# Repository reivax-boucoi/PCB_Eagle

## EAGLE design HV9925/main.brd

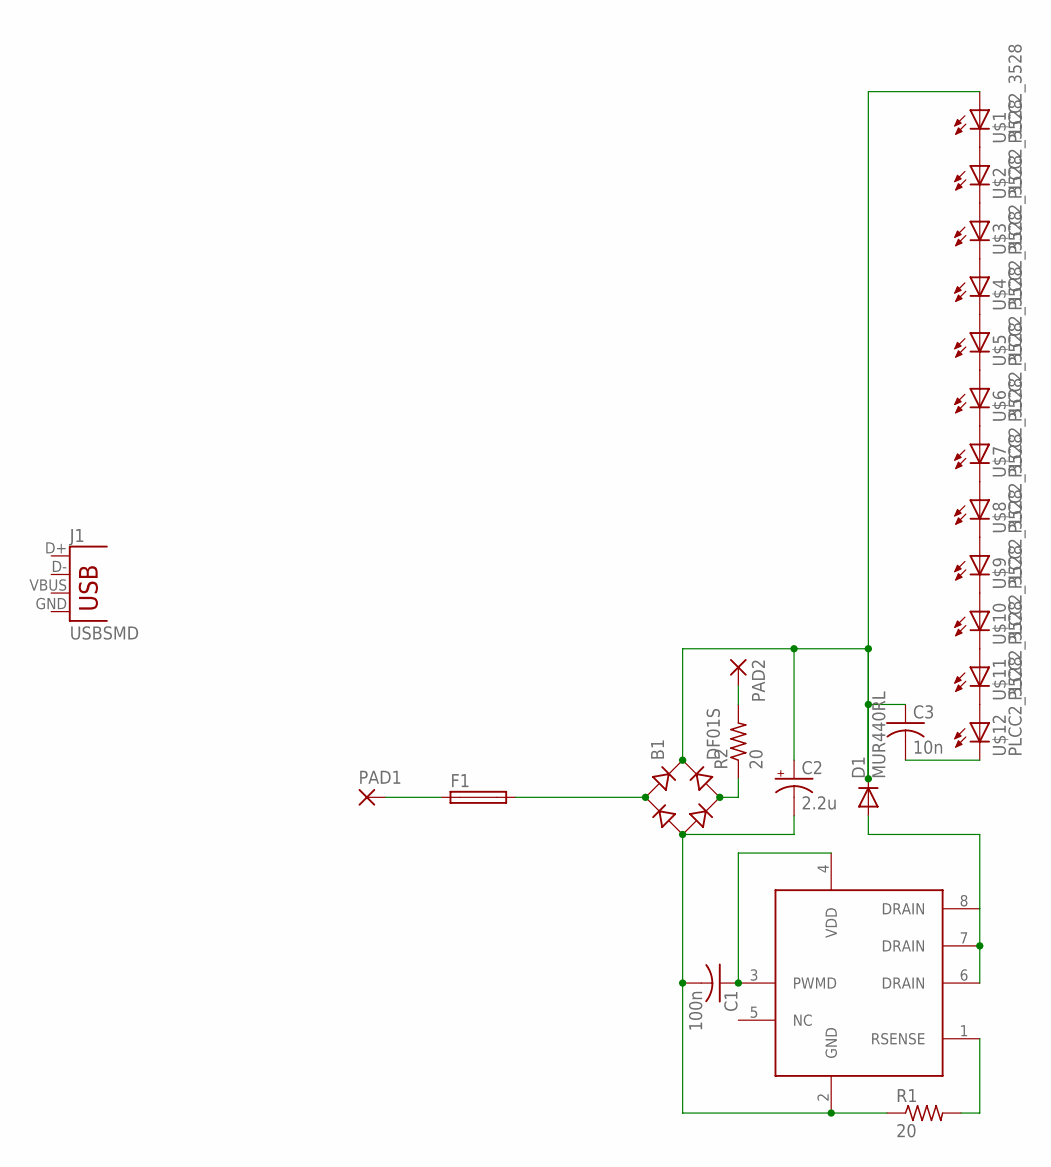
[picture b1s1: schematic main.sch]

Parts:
B1: DF01S; DFS
C1: 100n; C0603
C2: 2.2u; E3,5-8
C3: 10n; C025-025X050
D1: MUR440RL; C2673
F1: TE5
J1: USBSMD; USB-MINIB
PAD1, PAD2: 2,54/1,0
R1, R2: 20; R0805
U$1, U$2, U$3, U$4, U$5, U$6, U$7, U$8, U$9, U$10, U$11, U$12: PLCC2_3528
U$13: HV9925; SOIC-8

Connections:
unnamed: U$1.P$2 (C), U$2.P$1 (A)
unnamed: U$2.P$2 (C), U$3.P$1 (A)
unnamed: U$3.P$2 (C), U$4.P$1 (A)
unnamed: U$4.P$2 (C), U$5.P$1 (A)
unnamed: U$5.P$2 (C), U$6.P$1 (A)
unnamed: U$6.P$2 (C), U$7.P$1 (A)
unnamed: U$7.P$2 (C), U$8.P$1 (A)
unnamed: U$8.P$2 (C), U$9.P$1 (A)
unnamed: U$9.P$2 (C), U$10.P$1 (A)
unnamed: U$10.P$2 (C), U$11.P$1 (A)
unnamed: U$11.P$2 (C), U$12.P$1 (A)
unnamed: B1.AC1, F1.2
unnamed: PAD2.1, R2.2
unnamed: B1.+, C2.+, C3.1, D1.C, U$1.P$1 (A)
unnamed: B1.-, C1.2, C2.-, R1.1, U$13.2 (GND)
unnamed: F1.1, PAD1.1
unnamed: D1.A, U$13.6 (DRAIN), U$13.7 (DRAIN), U$13.8 (DRAIN)
unnamed: B1.AC2, R2.1
unnamed: C1.1, U$13.3 (PWMD), U$13.4 (VDD)
unnamed: R1.2, U$13.1 (RSENSE)
unnamed: C3.2, U$12.P$2 (C)

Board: 2 copper layers, 24 parts (0 on the bottom side), 21 nets, no tracks yet.

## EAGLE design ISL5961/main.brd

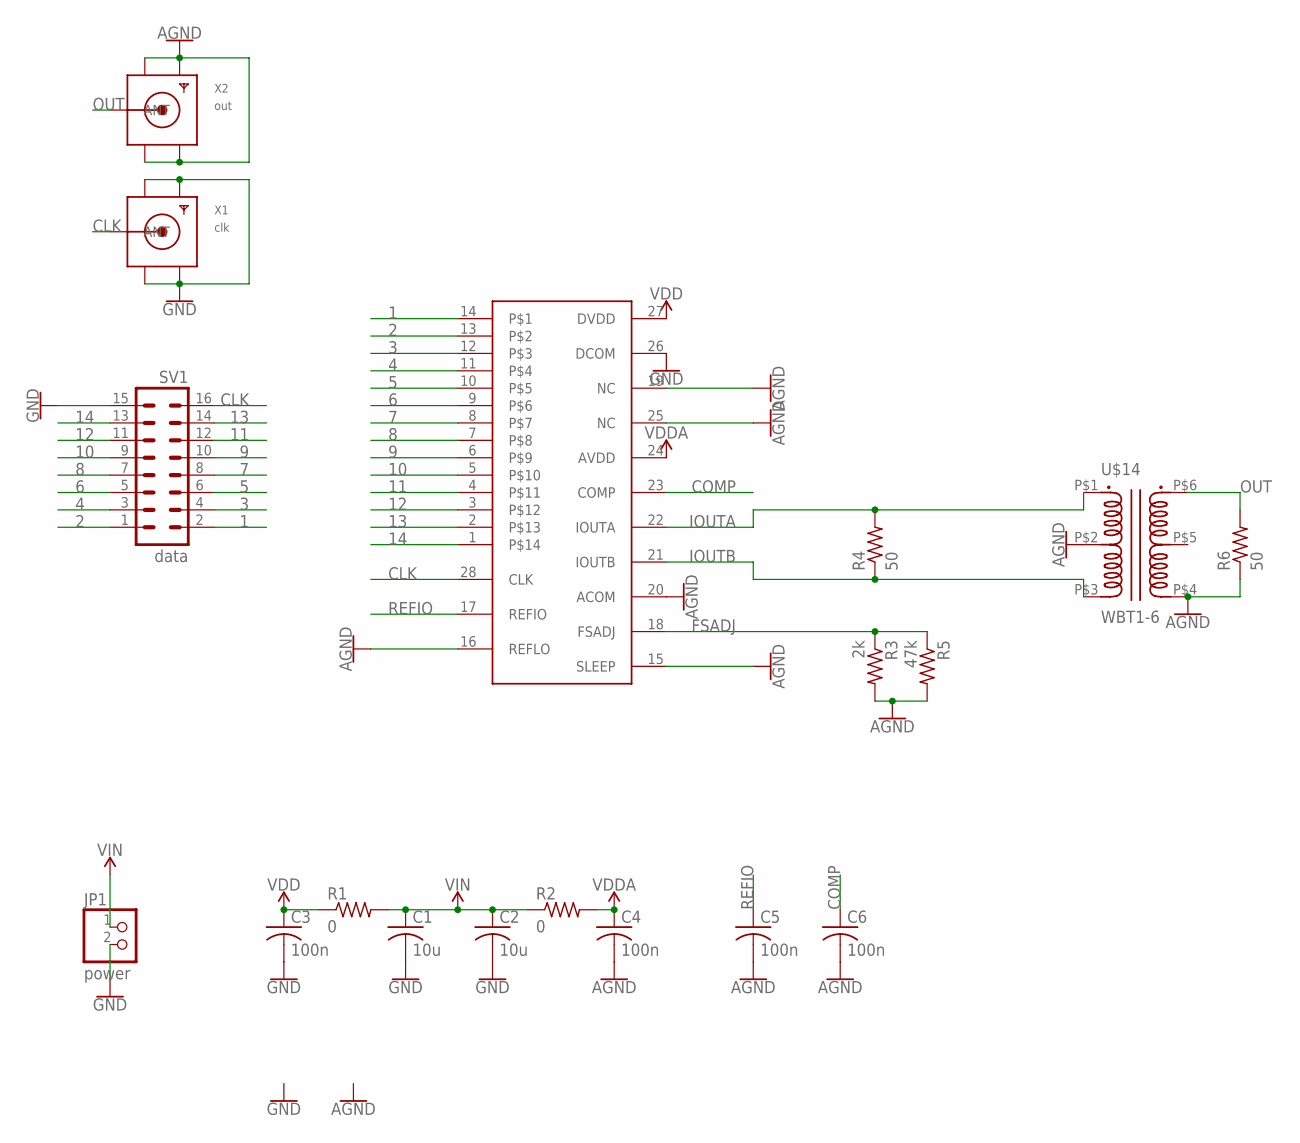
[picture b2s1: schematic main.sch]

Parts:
C1, C2: 10u; C0805K
C3, C4, C5, C6: 100n; C0603K
JP1: power; 1X02
R1, R2: 0; 0309/10
R3: 2k; R0603
R4, R6: 50; R0603
R5: 47k; R0603
SV1: data; MA08-2
U$1: ISL5961; TSSOP28
U$14: WBT1-6
X1: clk; SMA_EDGELAUNCH
X2: out; SMA_EDGELAUNCH

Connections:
1: SV1.2, U$1.14
2: SV1.1, U$1.13
3: SV1.4, U$1.12
4: SV1.3, U$1.11
5: SV1.6, U$1.10
6: SV1.5, U$1.9
7: SV1.8, U$1.8
8: SV1.7, U$1.7
9: SV1.10, U$1.6
10: SV1.9, U$1.5
11: SV1.12, U$1.4
12: SV1.11, U$1.3
13: SV1.14, U$1.2
14: SV1.13, U$1.1
AGND: C4.2, C5.2, C6.2, R3.2, R5.2, R6.1, U$1.15 (SLEEP), U$1.16 (REFLO), U$1.19 (NC), U$1.20 (ACOM), U$1.25 (NC), U$14.P$2 (1M), U$14.P$4 (2B), X2.GND@1 (GND4), X2.GND@2 (GND3), X2.GND@3 (GND2), X2.GND@4 (GND1)
CLK: SV1.16, U$1.28 (CLK), X1.P (ANT)
COMP: C6.1, U$1.23 (COMP)
FSADJ: R3.1, R5.1, U$1.18 (FSADJ)
GND: C1.2, C2.2, C3.2, JP1.2, SV1.15, U$1.26 (DCOM), X1.GND@1 (GND4), X1.GND@2 (GND3), X1.GND@3 (GND2), X1.GND@4 (GND1)
IOUTA: R4.2, U$1.22 (IOUTA), U$14.P$1 (1A)
IOUTB: R4.1, U$1.21 (IOUTB), U$14.P$3 (1B)
OUT: R6.2, U$14.P$6 (2A), X2.P (ANT)
REFIO: C5.1, U$1.17 (REFIO)
VDD: C3.1, R1.1, U$1.27 (DVDD)
VDDA: C4.1, R2.2, U$1.24 (AVDD)
VIN: C1.1, C2.1, JP1.1, R1.2, R2.1

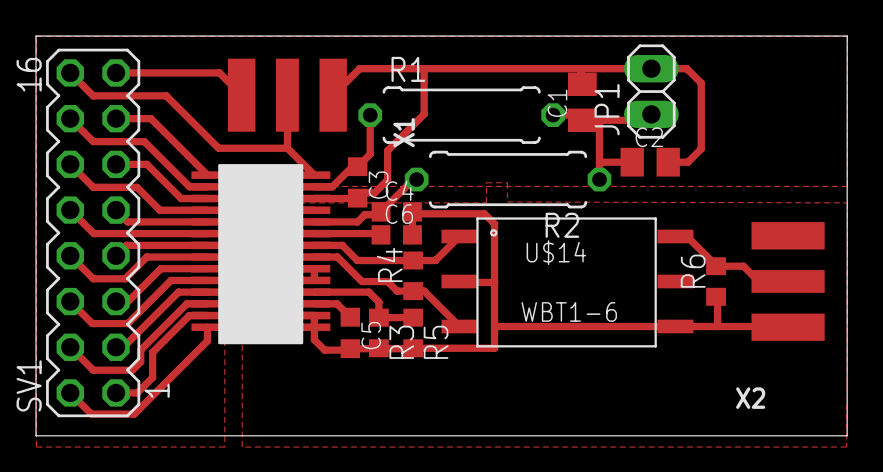
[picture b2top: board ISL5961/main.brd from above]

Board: 2 copper layers, 45.1 x 22.2 mm, 18 parts (0 on the bottom side), 26 nets.

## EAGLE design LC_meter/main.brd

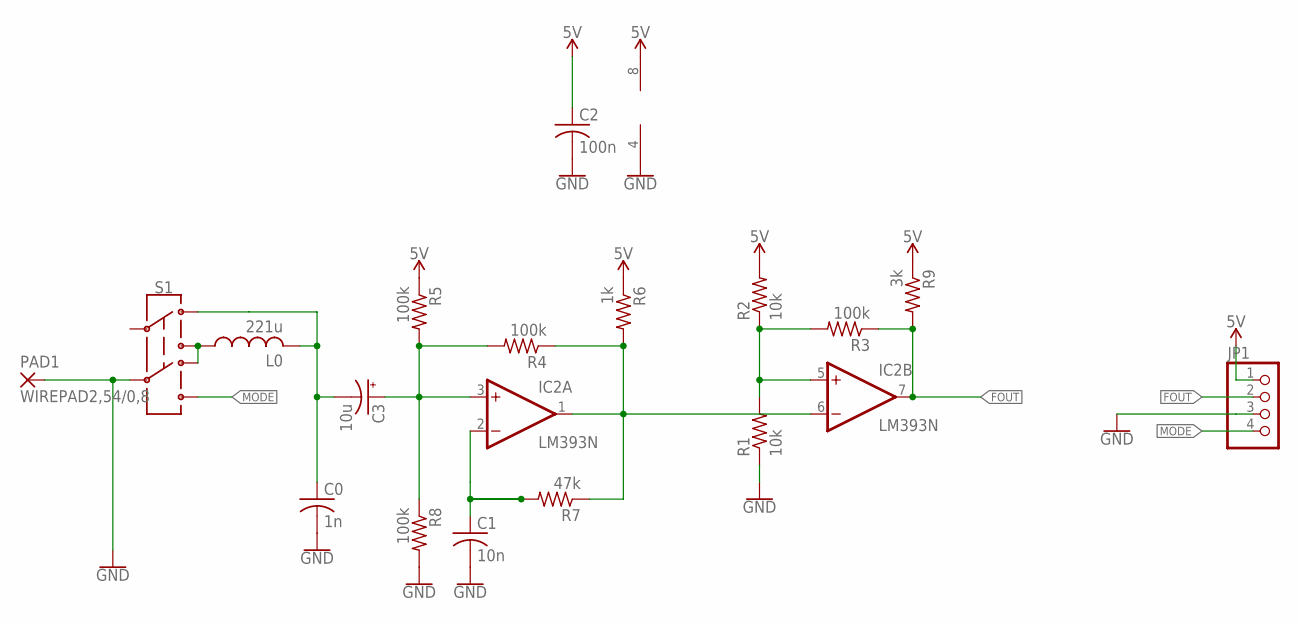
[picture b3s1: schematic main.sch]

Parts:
C0: 1n; C025-025X050
C1: 10n; C025-025X050
C2: 100n; C025-025X050
C3: 10u; E2,5-6
IC2: LM393N; DIL08
JP1: PINHD-1X4; 1X04
L0: 221u; 0204/5
PAD1: WIREPAD2,54/0,8; 2,54/0,8
R1: 10k; 0204/7
R2: 10k; 0207/10
R3, R4, R5, R8: 100k; 0207/10
R6: 1k; 0207/10
R7: 47k; 0207/10
R9: 3k; 0207/10
S1: SWITCH-DPDT-PTH-GPI-152-3013; SWITCH_DPDT_PTH_GPI-152-3013

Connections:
5V: C2.1, IC2.8 (V+), JP1.1, R2.2, R5.1, R6.1, R9.1
FOUT: IC2.7 (OUT), JP1.2, R3.1, R9.2
GND: C0.2, C1.2, C2.2, IC2.4 (V-), JP1.3, PAD1.1, R1.1, R8.2, S1.C@2 (5)
MODE: JP1.4, S1.21 (6)
unnamed: C1.1, IC2.2 (-IN), R7.2
unnamed: C3.+, IC2.3 (+IN), R4.2, R5.2, R8.1
unnamed: IC2.1 (OUT), IC2.6 (-IN), R4.1, R6.2, R7.1
unnamed: IC2.5 (+IN), R1.2, R2.1, R3.2
unnamed: C0.1, C3.-, L0.2, S1.10 (1)
unnamed: L0.1, S1.11 (4), S1.20 (3)

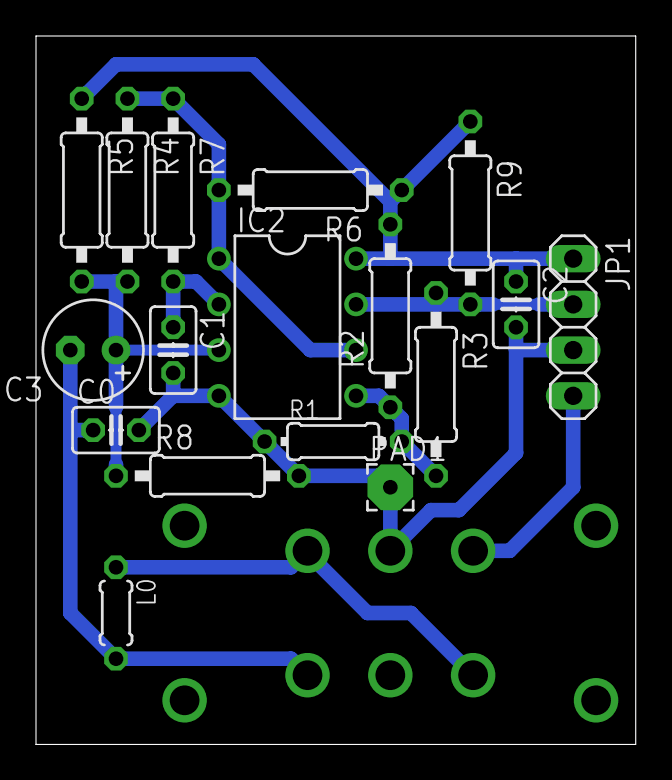
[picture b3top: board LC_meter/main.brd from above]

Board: 2 copper layers, 33.3 x 39.4 mm, 18 parts (1 on the bottom side), 10 nets.

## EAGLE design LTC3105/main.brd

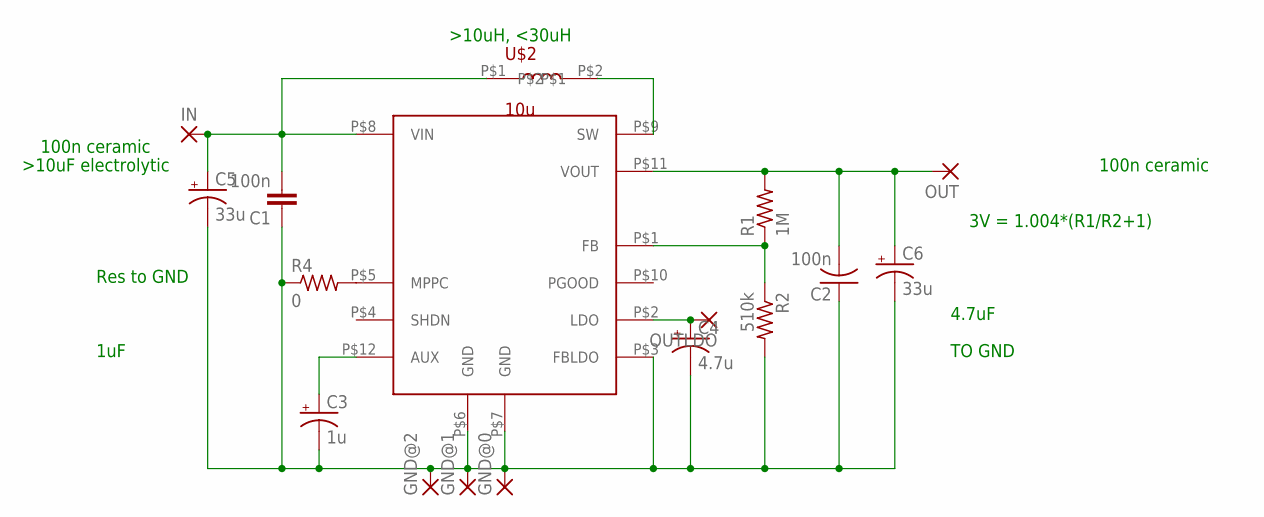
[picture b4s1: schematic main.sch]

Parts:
C1: 100n; C0603
C2: 100n; C025-025X050
C3: 1u; E1,8-4
C4: 4.7u; E1,8-4
C5, C6: 33u; E2-5
GND@0, GND@1, GND@2: 2,54/1,0
IN: 2,54/1,0
OUT: 2,54/1,0
OUTLDO: 2,54/1,0
R1: 1M; 0204V
R2: 510k; R0603
R4: 0; R0603
U$1: LTC3105; MSOP_12
U$2: 10u; DR0810

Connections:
GND: C1.1, C2.1, C3.-, C4.-, C5.-, C6.-, GND@0.1, GND@1.1, GND@2.1, R2.2, R4.1, U$1.P$3 (FBLDO), U$1.P$6 (GND), U$1.P$7 (GND)
unnamed: C4.+, OUTLDO.1, U$1.P$2 (LDO)
unnamed: R1.1, R2.1, U$1.P$1 (FB)
unnamed: C3.+, U$1.P$12 (AUX)
unnamed: C1.2, C5.+, IN.1, U$1.P$8 (VIN), U$2.P$1
unnamed: U$1.P$9 (SW), U$2.P$2
unnamed: C2.2, C6.+, OUT.1, R1.2, U$1.P$11 (VOUT)
unnamed: R4.2, U$1.P$5 (MPPC)

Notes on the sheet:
100n ceramic
1uF
3V = 1.004*(R1/R2+1)
Res to GND
TO GND
4.7uF

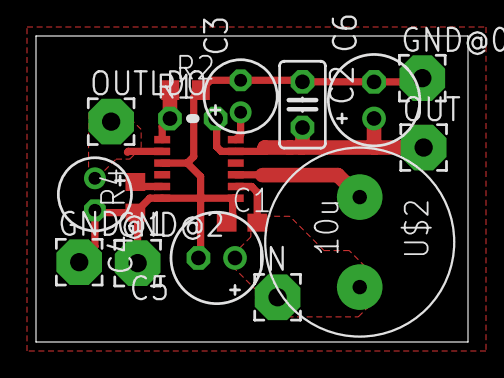
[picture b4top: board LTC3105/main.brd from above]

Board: 2 copper layers, 24.0 x 17.0 mm, 17 parts (0 on the bottom side), 8 nets.

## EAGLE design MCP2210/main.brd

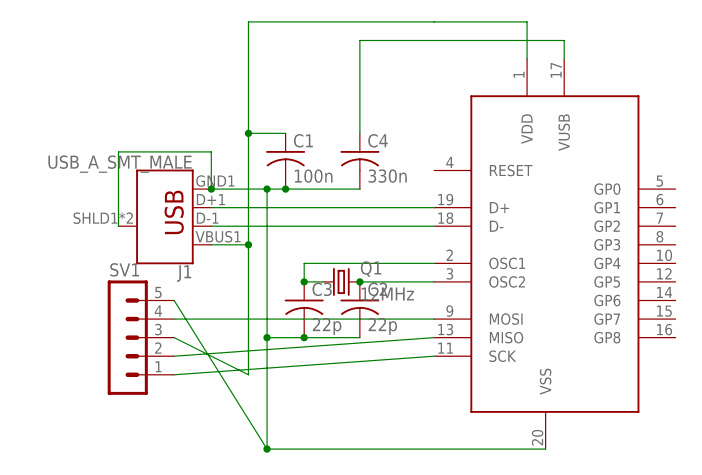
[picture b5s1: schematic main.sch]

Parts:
C1: 100n; C0805
C2, C3: 22p; C0603
C4: 330n; C0603
J1: USB_A_SMT_MALE; USB-A-SMT-MALE
Q1: 12MHz; HC49U-V
SV1: MA05-1
U$1: MCP2210; SOIC20_GENERIC

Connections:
GND: C1.2, C2.2, C3.2, C4.2, J1.GND1 (GND), J1.SHLD1 (SHIELD), J1.SHLD2 (SHIELD), SV1.5, U$1.20 (VSS)
unnamed: J1.D+1 (D+), U$1.19 (D+)
unnamed: J1.D-1 (D-), U$1.18 (D-)
unnamed: C1.1, J1.VBUS1 (VBUS), SV1.3, U$1.1 (VDD)
unnamed: C3.1, Q1.1, U$1.2 (OSC1)
unnamed: C2.1, Q1.2, U$1.3 (OSC2)
unnamed: C4.1, U$1.17 (VUSB)
unnamed: SV1.1, U$1.11 (SCK)
unnamed: SV1.2, U$1.13 (MISO)
unnamed: SV1.4, U$1.9 (MOSI)

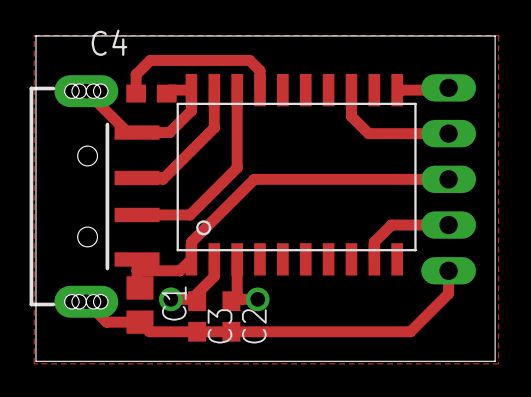
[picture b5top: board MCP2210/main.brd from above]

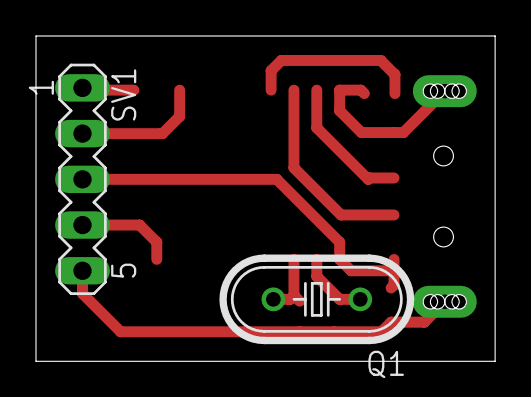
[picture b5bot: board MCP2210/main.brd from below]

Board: 2 copper layers, 25.5 x 18.1 mm, 8 parts (2 on the bottom side), 10 nets.

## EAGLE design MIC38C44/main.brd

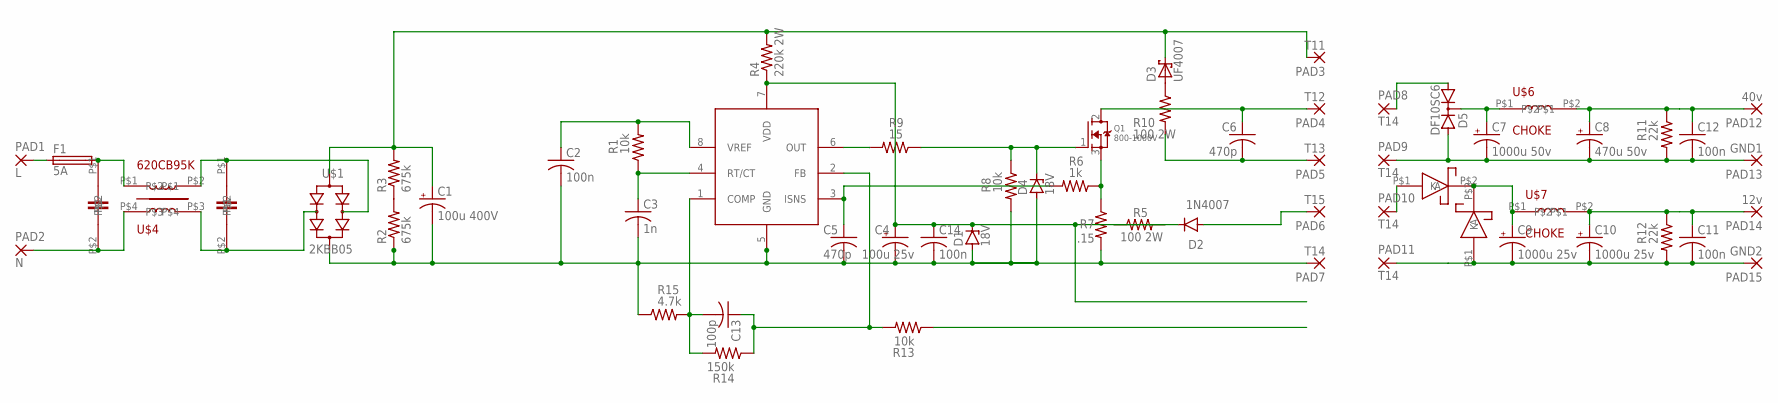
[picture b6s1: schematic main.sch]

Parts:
C1: 100u 400V; EB25D
C2, C11, C12, C14: 100n; C050-035X075
C3: 1n; C050-035X075
C4: 100u 25v; E2,5-6
C5, C6: 470p; C050-035X075
C7: 1000u 50v; E5-13
C8: 470u 50v; E5-10,5
C9, C10: 1000u 25v; E5-10,5
C13: 100p; C050-035X075
D1, D4: 18V; ZDIO-7.5
D2: 1N4007; DO41-10
D3: UF4007; DO35-7
D5: DF10SC6; TO220ABS
D7, D8: SS34; DO-214AB
F1: 5A; SH22,5
PAD1: L; 2,54/1,0
PAD2: N; 2,54/1,0
PAD3: T11; 2,54/1,0
PAD4: T12; 2,54/1,0
PAD5: T13; 2,54/1,0
PAD6: T15; 2,54/1,0
PAD7, PAD8, PAD9, PAD10, PAD11: T14; 2,54/1,0
PAD12: 40v; 2,54/1,0
PAD13: GND1; 2,54/1,0
PAD14: 12v; 2,54/1,0
PAD15: GND2; 2,54/1,0
Q1: 800-1000V; TO220V
R1, R8, R13: 10k; 0207/7
R2, R3: 675k; 0207/7
R4: 220k 2W; P0613/15
R5, R10: 100 2W; 0617V
R6: 1k; 0207/10
R7: .15; 0207/7
R9: 15; 0207/7
R11, R12: 22k; 0207/7
R14: 150k; 0207/7
R15: 4.7k; 0207/2V
U$1: 2KBB05
U$2, U$3: 100n; C_X2
U$4: 620CB95K; 602CB95K
U$5: MIC3844; DIL08
U$6, U$7: CHOKE

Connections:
12V: C10.+, C11.1, PAD14.1, R12.1, U$7.P$2
12VRECT: C9.+, D7.P$2 (K), D8.P$2 (K), U$7.P$1
40V: C8.+, C12.1, PAD12.1, R11.1, U$6.P$2
40VRECT: C7.+, D5.C, U$6.P$1
COMP: C13.2, R14.2, R15.2, U$5.1 (COMP)
DRAIN: Q1.3 (S), R6.1, R7.1
DRV: R9.2, U$5.6 (OUT)
FB: C13.1, R13.2, R14.1, U$5.2 (FB)
GATE: D4.C, Q1.1 (G), R8.1, R9.1
GND: C1.-, C2.2, C3.2, C4.-, C5.2, C14.2, D1.A, D4.A, PAD7.1, R2.1, R7.2, R8.2, R15.1, U$1.+, U$5.5 (GND)
GND1: C7.-, C8.-, C12.2, D5.A2, PAD9.1, PAD13.1, R11.2
GND2: C9.-, C10.-, C11.2, D7.P$1 (A), PAD11.1, PAD15.1, R12.2
unnamed: PAD2.1, U$3.P$2, U$4.P$4
unnamed: U$1.AC@1 (AC), U$2.P$2, U$4.P$3
unnamed: U$1.AC@2 (AC), U$2.P$1, U$4.P$2
unnamed: F1.2, U$3.P$1, U$4.P$1
unnamed: F1.1, PAD1.1
unnamed: R2.2, R3.1
unnamed: D2.C, R5.1
unnamed: C5.1, R6.2, U$5.3 (ISNS)
unnamed: D2.A, PAD6.1
unnamed: D3.A, R10.1
unnamed: C6.2, PAD5.1, R10.2
unnamed: D5.A1, PAD8.1
unnamed: D8.P$1 (A), PAD10.1
RTCT: C3.1, R1.1, U$5.4 (RT/CT)
SOURCE: C6.1, PAD4.1, Q1.2 (D)
V+: C1.+, D3.C, PAD3.1, R3.2, R4.2, U$1.-
VDD: C4.+, C14.1, D1.C, R4.1, R5.2, U$5.7 (VDD)
VREF: C2.1, R1.2, U$5.8 (VREF)

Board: 2 copper layers, 60 parts (0 on the bottom side), 30 nets, no tracks yet.

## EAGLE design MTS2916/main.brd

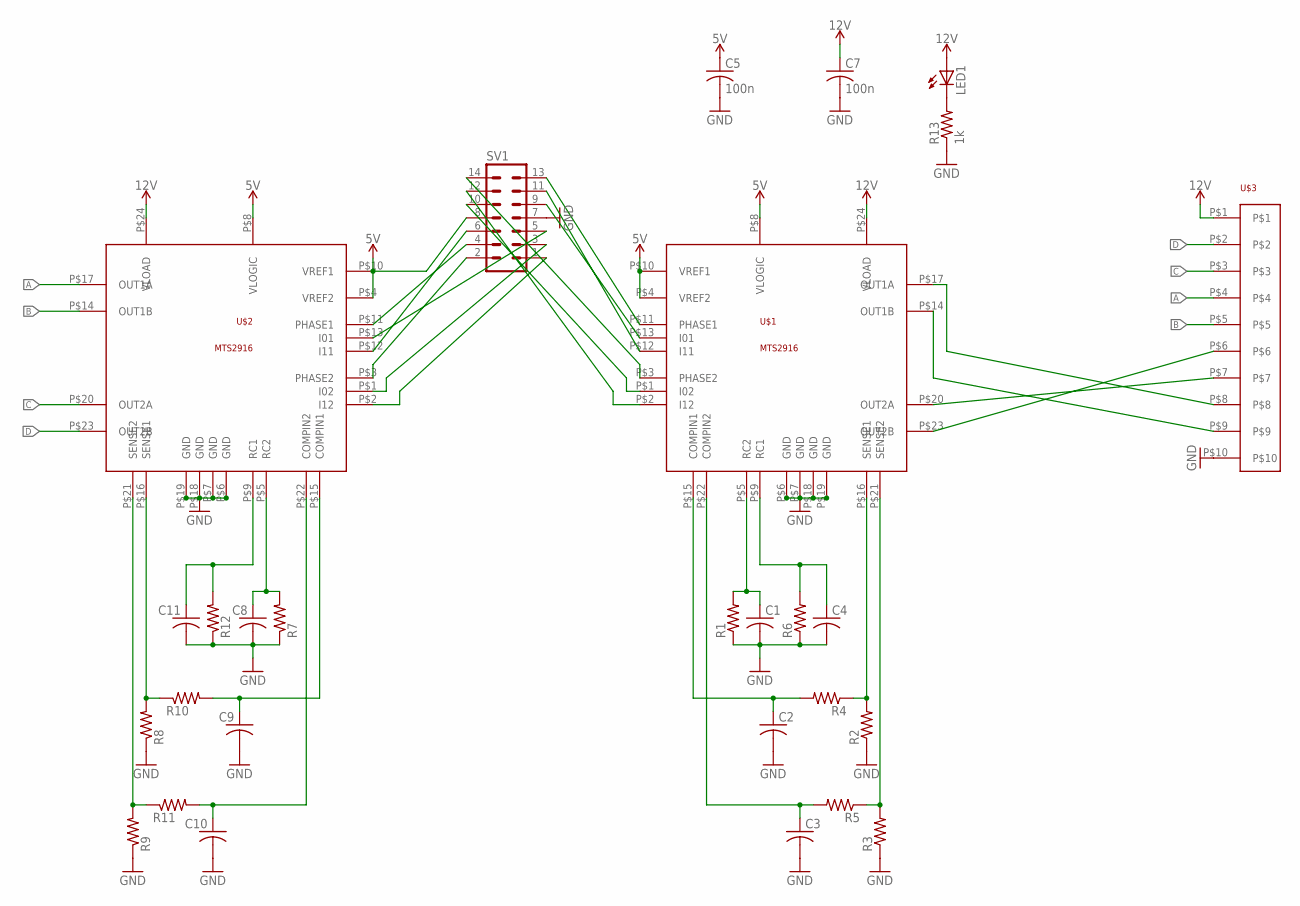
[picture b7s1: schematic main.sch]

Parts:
C1, C2, C3, C4, C8, C9, C10, C11: C-US025-024X044; C025-024X044
C5, C7: 100n; C0603
LED1: LED_ESML0603; LED_SML0603
R1, R2, R3, R4, R5, R6, R7, R8, R9, R10, R11, R12: R-US_M0805; M0805
R13: 1k; R0603
SV1: MA07-2
U$1, U$2: MTS2916; SOP24
U$3: SCREWTERM_5MM_10WAY

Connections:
5V: C5.1, SV1.8, U$1.P$4 (VREF2), U$1.P$8 (VLOGIC), U$1.P$10 (VREF1), U$2.P$4 (VREF2), U$2.P$8 (VLOGIC), U$2.P$10 (VREF1)
12V: C7.1, LED1.A, U$1.P$24 (VLOAD), U$2.P$24 (VLOAD), U$3.P$1
A: U$2.P$17 (OUT1A), U$3.P$4
B: U$2.P$14 (OUT1B), U$3.P$5
C: U$2.P$20 (OUT2A), U$3.P$3
D: U$2.P$23 (OUT2B), U$3.P$2
GND: C1.2, C2.2, C3.2, C4.2, C5.2, C7.2, C8.2, C9.2, C10.2, C11.2, R1.1, R2.1, R3.1, R6.1, R7.1, R8.1, R9.1, R12.1, R13.1, SV1.7, U$1.P$6 (GND), U$1.P$7 (GND), U$1.P$18 (GND), U$1.P$19 (GND), U$2.P$6 (GND), U$2.P$7 (GND), U$2.P$18 (GND), U$2.P$19 (GND), U$3.P$10
unnamed: U$1.P$23 (OUT2B), U$3.P$6
unnamed: R2.2, R4.1, U$1.P$16 (SENSE1)
unnamed: R3.2, R5.1, U$1.P$21 (SENSE2)
unnamed: C3.1, R5.2, U$1.P$22 (COMPIN2)
unnamed: C2.1, R4.2, U$1.P$15 (COMPIN1)
unnamed: R8.2, R10.1, U$2.P$16 (SENSE1)
unnamed: R9.2, R11.1, U$2.P$21 (SENSE2)
unnamed: C10.1, R11.2, U$2.P$22 (COMPIN2)
unnamed: C1.1, R1.2, U$1.P$5 (RC2)
unnamed: C4.1, R6.2, U$1.P$9 (RC1)
unnamed: C9.1, R10.2, U$2.P$15 (COMPIN1)
unnamed: C8.1, R7.2, U$2.P$5 (RC2)
unnamed: C11.1, R12.2, U$2.P$9 (RC1)
unnamed: SV1.13, U$1.P$11 (PHASE1)
unnamed: SV1.9, U$1.P$13 (I01)
unnamed: SV1.11, U$1.P$12 (I11)
unnamed: SV1.14, U$1.P$3 (PHASE2)
unnamed: SV1.10, U$1.P$1 (I02)
unnamed: SV1.12, U$1.P$2 (I12)
unnamed: SV1.4, U$2.P$11 (PHASE1)
unnamed: SV1.5, U$2.P$13 (I01)
unnamed: SV1.6, U$2.P$12 (I11)
unnamed: SV1.2, U$2.P$3 (PHASE2)
unnamed: SV1.3, U$2.P$1 (I02)
unnamed: SV1.1, U$2.P$2 (I12)
unnamed: U$1.P$20 (OUT2A), U$3.P$7
unnamed: U$1.P$14 (OUT1B), U$3.P$9
unnamed: U$1.P$17 (OUT1A), U$3.P$8
unnamed: LED1.C, R13.2

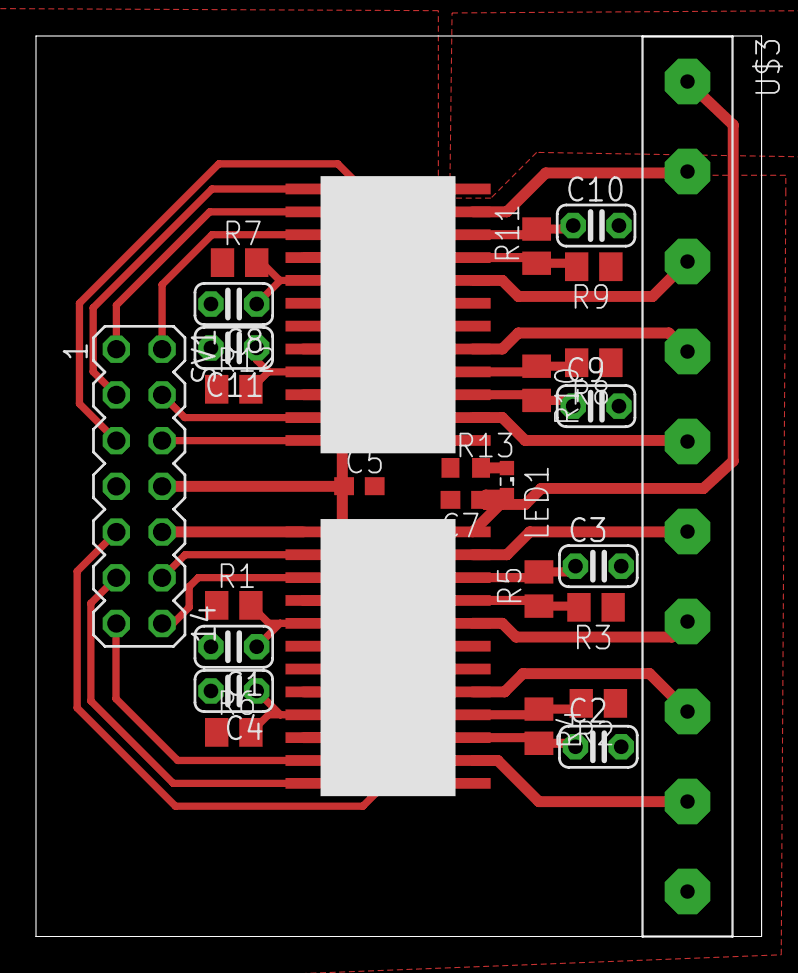
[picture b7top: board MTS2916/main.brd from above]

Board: 2 copper layers, 40.3 x 50.0 mm, 28 parts (0 on the bottom side), 36 nets.

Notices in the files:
parts and their libraries:
SparkFun-Retired: Licensing: Creative Commons ShareAlike 4.0 International - https://creativecommons.org/licenses/by-sa/4.0
